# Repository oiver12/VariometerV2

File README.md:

# VariometerV2

A paragliding variometer built from custom KiCad PCBs, ESP32 firmware, sensor fusion, and an e-ink flight interface.

Flight-tested on my paragliding harness. [Watch the flight video](docs/media/flight.mp4).

I started this project in 2021 as my [**Maturarbeit**](https://github.com/oiver12/Variometer-Maturarbeit) (Swiss high-school thesis), then continued developing it independently through 2024. I designed the custom PCBs and developed the firmware, sensor fusion pipeline, and e-ink rendering system, screens, and widgets. The enclosure/CAD work combines contributions from my brother and me.

## Features

- Three custom PCB revisions designed in KiCad.
- ESP32 firmware in C on ESP-IDF and FreeRTOS.
- BMI088 IMU, DPS310 barometer, and QMC5883L magnetometer; quaternion orientation estimation and a Kalman filter combining barometric altitude with acceleration.
- GPS/NMEA input, IGC flight logging, airspace parsing, sound output, an experimental BLE module, and watchdog support.
- E-ink UI with a custom rendering system, screens, and widgets.
- Sensor mocks, a FreeRTOS host simulation, a Linux screen simulator, and recorded-sensor replay for analysis.

## Hardware

### Latest revision: 2.1

| Front / top | Back / mirrored bottom |
| --- | --- |
|  |  |

[Schematic overview](docs/images/schematic-2.1/VariometerV2.2.1.svg) · [Power](docs/images/schematic-2.1/VariometerV2.2.1-Power.svg) · [Sensors](docs/images/schematic-2.1/VariometerV2.2.1-Devices.svg) · [Display](docs/images/schematic-2.1/VariometerV2.2.1-Screen.svg) · [Peripherals](docs/images/schematic-2.1/VariometerV2.2.1-Peripherals.svg)

### Revision history

| Revision | Design files | PCB views | Schematic |
| --- | --- | --- | --- |
| 1.0 | [Hardware/Version 1.0](Hardware/Version%201.0/) | [Top](docs/images/pcb-1.0-top.svg) · [bottom](docs/images/pcb-1.0-bottom.svg) · [3D](docs/images/pcb-1.0-3d.png) | [SVG](docs/images/schematic-1.0/VariometerV2.svg) |
| 2.0 | [Hardware/Version 2.0](Hardware/Version%202.0/) | [Top](docs/images/pcb-2.0-top.svg) · [bottom](docs/images/pcb-2.0-bottom.svg) · [3D](docs/images/pcb-2.0-3d.png) | [SVG](docs/images/schematic-2.0/VariometerV2.2.svg) |
| 2.1 | [Hardware/Version 2.1](Hardware/Version%202.1/) | [Top](docs/images/pcb-2.1-top.svg) · [bottom](docs/images/pcb-2.1-bottom.svg) · [3D](docs/images/pcb-2.1-3d.png) | [SVG overview](docs/images/schematic-2.1/VariometerV2.2.1.svg) |

`Case/` contains the enclosure designs and printing exports.

## Firmware architecture

```mermaid
flowchart LR
    IMU["BMI088 IMU"] --> Drivers["Sensor drivers"]
    Baro["DPS310 barometer"] --> Drivers
    Mag["QMC5883L magnetometer"] --> Drivers
    Drivers --> Orientation["Quaternion orientation"]
    Orientation --> Acc["Vertical acceleration"]
    Drivers --> Kalman["Kalman altitude and climb rate"]
    Acc --> Kalman
    GPS["GPS / NMEA"] --> State["Flight state / device context"]
    Kalman --> State
    Airspace["Airspace parser"] --> State
    State --> UI["E-ink UI / screens / widgets"]
    State --> IGC["IGC logger"]
    State --> BLE["BLE module (experimental)"]
    State --> Sound["Sound"]
```

The sensor fusion pipeline runs across FreeRTOS tasks: the barometer task notifies the Kalman filter, while the acceleration task updates orientation and queues vertical acceleration. The filter combines these inputs into shared flight state, using queues, task notifications, and mutexes to coordinate the tasks.

Rendering and e-ink refresh run in separate tasks. GPS parsing, IGC logging, button input, battery management, sound, storage checks, and airspace parsing have their own task entry points.

### Project structure

| Directory | Purpose |
| --- | --- |
| `Hardware/`, `Case/` | PCB revisions and enclosure designs |
| `Software/variometer-software/` | ESP32 firmware |
| `Simulation/Main/` | FreeRTOS host runner and sensor mocks |
| `Screen_Simulator_Linux/`, `Screen_Simulator/` | Desktop UI simulators |
| `VariometerAnalysis/` | Sensor-log analysis and offline replay |

## Simulation & replay

Sensor mocks replace hardware reads with recorded IMU, magnetometer, and pressure samples. A FreeRTOS simulation replays these recordings on a PC, allowing the firmware to run against recorded data.

The offline analysis tool runs the firmware’s quaternion and Kalman functions over the recorded sensor data:

Barometric altitude and climb rate compared with the Kalman estimate. The recording has no timestamps, so replay uses an assumed sample interval; this plot is not a latency benchmark.

The Linux screen simulator exercises the custom UI independently of the device:

| Flight layout | Navigation layout | Settings |
| --- | --- | --- |
|  |  |  |

[Replay and simulator instructions](docs/development.md#simulation--replay).

## Build & flash

**ESP32-S3 · ESP-IDF v5.1.4**

See the [developer guide](docs/development.md) for cloning, firmware build and flash commands, desktop simulation, and regenerating the visuals.

## Flight footage

## Third-party code & license

The project builds on FreeRTOS, Waveshare’s e-ink driver and GUI, STMicroelectronics bitmap fonts, Neil Kolban’s BLE library, Freescale/NXPMotionSense sensor fusion, kalman-clib, and other credited libraries. Full credits and license details are in [THIRD_PARTY_NOTICES.txt](THIRD_PARTY_NOTICES.txt).

**My original software is licensed under [MIT](LICENSE).** Third-party code retains its own licenses, including the FIFO’s **GPL-3.0-or-later** obligations; the combined tree is not uniformly MIT-licensed. Enclosure/CAD contributions and third-party assets are outside this software license unless separately stated.

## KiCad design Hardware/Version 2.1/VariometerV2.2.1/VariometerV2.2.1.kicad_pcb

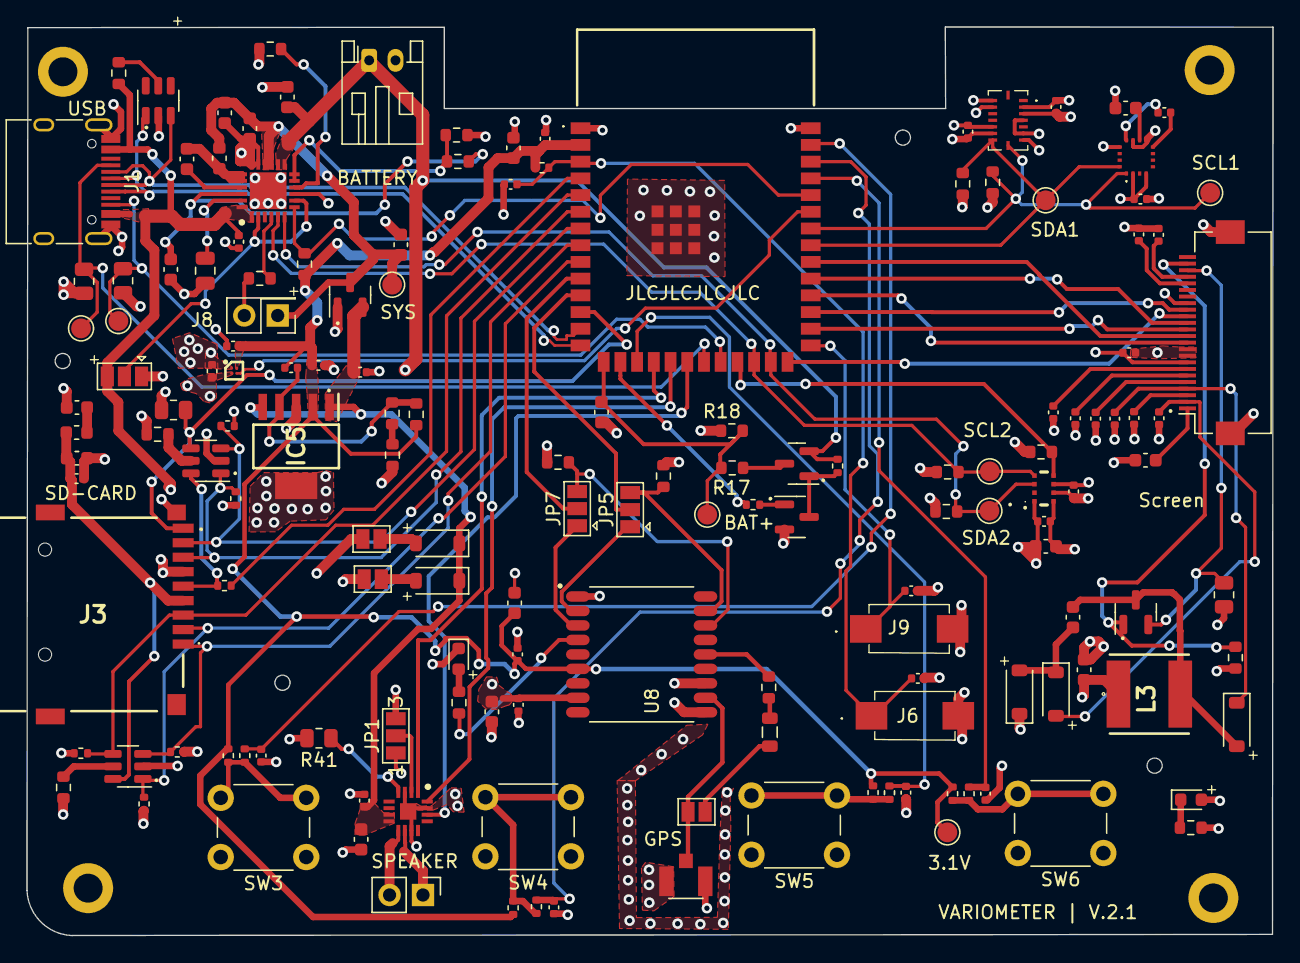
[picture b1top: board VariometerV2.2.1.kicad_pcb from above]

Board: 4 copper layers, 94.7 x 69.1 mm, 158 parts (0 on the bottom side), 100 nets.

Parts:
C1: 22uF; C_0603_1608Metric
C2, C6, C11, C15, C16, C19, C23, C24, C25, C26, C27, C28, C29, C31, C32, C47, C48, C49: 1uF; C_0402_1005Metric
C3, C4, C5, C8, C17, C20, C35, C36, C37, C38, C39, C43, C50: 100nF; C_0402_1005Metric
C7, C13, C14, C30, C42, C44, C45, C52: 10uF; C_0603_1608Metric
C9, C33, C34, C40, C46: 4.7uF; C_0603_1608Metric
C10: 6.8uF; C_0805_2012Metric
C12: 47nF; C_0603_1608Metric
C18: 10nF; C_0402_1005Metric
C21, C22: 2.2uF; C_0603_1608Metric
C41: 220nF; C_0402_1005Metric
C51: 1uF; C_0603_1608Metric
D1, D3, D4, D5, D6: B5819W SL; D_SOD-123
D2: RED; LED_0603_1608Metric
D7: BLUE; LED_0603_1608Metric
FB1: 600 @ 100 MHz; L_0603_1608Metric
H1, H2, H3, H4: MountingHole_Pad; MountingHole_2.2mm_M2_DIN965_Pad
IC1: ESP32-S3-WROOM; ESP32S3WROOM1
IC3: BQ24196RGER; QFN50P400X400X100-25N-D
IC4: TPS22916CNYFPR; BGA4C40P2X2_78X78X50
IC5: TPS73701DCQR; SOT127P706X180-6N
J1: USB_C_Receptacle_USB2.0; USB_C_Receptacle_HRO_TYPE-C-31-M-12
J2: Conn_01x02; PinHeader_1x02_P2.54mm_Vertical
J3: TFP09212B
J5: U.FL-R-SMT(01); HRS_U.FL-R-SMT(01)
J6, J9: SW; PTS636SM25FSMTRLFS
J7: Conn_01x02; JST_PH_S2B-PH-K_1x02_P2.00mm_Horizontal
J8: LED_CHRG; PinHeader_2x01_P2.54mm_Vertical
J10: Conn_01x24_MountingPin; Hirose_FH12-24S-0.5SH_1x24-1MP_P0.50mm_Horizontal
JP1: SolderJumper_3_Open; SolderJumper-3_P1.3mm_Open_Pad1.0x1.5mm_NumberLabels
JP2, JP4: JMP; SolderJumper-2_P1.3mm_Open_Pad1.0x1.5mm
JP5, JP7: SolderJumper-3_P1.3mm_Open_Pad1.0x1.5mm
JP6: SJ; SolderJumper-2_P1.3mm_Open_Pad1.0x1.5mm
JP8: SJMP; SolderJumper-3_P1.3mm_Open_Pad1.0x1.5mm
L1: 1uH P; L_0603_1608Metric
L2: 47nH; L_0805_2012Metric
L3: SRN6045TA-680M; SRN6045TA
Q1, Q2: AO3401A; SOT-23
Q3, Q4: AO3400A; SOT-23
R1, R5, R20, R27, R28, R29, R30, R31, R44, R46, R48: 10k; R_0402_1005Metric
R2, R3: 5.1k; R_0805_2012Metric
R4, R7, R8, R15, R17, R25, R26, R35, R37, R38, R39, R40, R42, R43: 10k; R_0603_1608Metric
R6, R45, R47, R49: 1k; R_0402_1005Metric
R9, R13: 1k; R_0603_1608Metric
R10: 10R; R_0603_1608Metric
R16: 270R; R_0603_1608Metric
R18: 15k; R_0603_1608Metric
R19: 1M; R_0402_1005Metric
R21: 47k; R_0603_1608Metric
R22: 20k; R_0603_1608Metric
R23: 9.1k; R_0603_1608Metric
R24: 1.5k; R_0603_1608Metric
R32: 10k S; R_0805_2012Metric
R33: 22; R_0402_1005Metric
R34: 0.47R; R_0805_2012Metric
R36: 100k; R_0603_1608Metric
R41: 10k B; R_0805_2012Metric
SW3, SW4, SW5, SW6: BTN1; SW_PUSH_6mm_H4.3mm
TP1: TP_BATTERY; TestPoint_Pad_D1.5mm
TP2: 3.1V TP; TestPoint_Pad_D1.5mm
TP3: TP_SDA1; TestPoint_Pad_D1.5mm
TP4: TP_SCL1; TestPoint_Pad_D1.5mm
TP5: TP_SDA2; TestPoint_Pad_D1.5mm
TP6: TP_SCL2; TestPoint_Pad_D1.5mm
TP10: TP_SYS_LOAD; TestPoint_Pad_D1.5mm
TP11: CC1; TestPoint_Pad_D1.5mm
TP12: CC2; TestPoint_Pad_D1.5mm
U1, U2, U3: SRV05-4; SOT-23-6
U4: DPS310; DPS310XTSA1
U5: BMI088
U6: QMC5883L
U7: MAX98357A; QFN50P300X300X80-17N
U8: L76-L; XCVR_L76-L

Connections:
3.1V_SDCARD: C20.1, C21.1, FB1.1, J3.4 (VDD), U2.6 (IO4)
+3.1V_SW: C7.1, C8.1, C17.1, C24.2, C33.1, C35.1, C36.1, C37.1, C38.1, C39.1, C52.1, D2.2 (A), IC4.A1 (VOUT), J10.9, J10.10, JP1.1 (A), L3.1, R7.1, R8.1, R25.1, R26.1, R27.1, R28.1, R29.1, R30.1, R31.1, R32.1, R37.1, R38.1, R39.1, R40.1, R41.1, U4.6 (VDDIO), U4.8 (VDD), U5.3 (VDD), U5.7 (PS), U5.11 (VDDIO), U5.14 (CSB1), U6.2 (VDD), U6.4 (S1), U6.13 (VDDIO), U7.4 (SD_MODE), U8.8 (VCC)
+3.1V_UNSW: C1.1, C3.1, C9.1, C15.1, C18.1, C19.1, C50.1, IC1.2 (3V3), IC4.A2 (VIN), IC5.2 (Vout), R1.1, R5.1, R15.1, R21.1, R44.1, R46.1, R48.1, TP2.1, U8.6 (V_BCKP)
+3.3V: C22.1, FB1.2
+5V: C11.1, IC3.1 (VBUS1), IC3.24 (VBUS2), J1.A4 (VBUS), J1.A9 (VBUS), J1.B4 (VBUS), J1.B9 (VBUS), JP2.2 (B), JP8.3 (B), R4.1
+BATT: C13.1, IC3.13 (BAT1), IC3.14 (BAT2), J7.1, JP4.2 (B), Q2.2 (S), R19.2
/Devices/GPS_RX: JP7.1 (A), U8.3 (RXD)
/Devices/GPS_SCL: JP5.3 (B), R8.2, U8.17 (I2C_SCL)
/Devices/GPS_SDA: JP7.3 (B), R7.2, U8.16 (I2C_SDA)
/Devices/GPS_TX: JP5.1 (A), U8.2 (TXD)
/Devices/GPS_VCCREF: R10.2, U8.14 (VCC_RF)
/Power/REGN: C46.1, IC3.22 (REGN), R42.1
/Power/STAT: IC3.4 (STAT), R13.2
/Power/SYS: C14.1, C44.1, C45.1, IC3.15 (SYS1), IC3.16 (SYS2), J8.1, L1.2, Q1.3 (D), TP10.1
/Power/TS: IC3.11 (TS1), IC3.12 (TS2), R42.2, R43.1
/Screen/GDR: J10.23, Q4.1 (G), R35.2
/Screen/PREVGH: C27.2, D3.1 (K), J10.4
/Screen/PREVGL: C29.2, D4.2 (A), J10.2
/Screen/RESE: J10.22, Q4.2 (S), R34.2
AUDIO_OUTN: J2.1, U7.10 (OUTN)
AUDIO_OUTP: J2.2, U7.9 (OUTP)
BAT_ADC: C51.1, IC1.15 (IO3), R17.1, R18.2, TP1.1
BAT_MS: IC1.16 (IO46), R20.1
BUTTON_1: C6.1, IC1.39 (IO1), R6.2
BUTTON_2: C47.1, IC1.38 (IO2), R45.2
BUTTON_3: C48.1, IC1.17 (IO9), R47.2
BUTTON_4: C49.1, IC1.37 (TXD0), R49.2
CHARG_INT: IC1.36 (RXD0), IC3.7 (INT), R15.2
EN: C2.1, C4.1, IC1.3 (EN), J6.1 (COM), R1.2
GND: C1.2, C2.2, C3.2, C4.2, C5.2, C6.2, C7.2, C8.2, C9.2, C10.2, C11.2, C13.2, C14.2, C15.2, C16.2, C17.2, C19.2, C20.2, C21.2, C22.2, C23.1, C24.1, C25.1, C26.1, C27.1, C28.1, C29.1, C30.1, C31.1, C32.1, C33.2, C35.2, C36.2, C37.2, C38.2, C39.2, C40.2, C42.2, C43.2, C44.2, C45.2, C46.2, C47.2, C48.2, C49.2, C50.2, C51.2, C52.2, D5.1 (K), D7.1 (K), H1.1, H2.1, H3.1, H4.1, IC1.1 (GND_1), IC1.40 (GND_2), IC1.41 (GND_3), IC1.42 (GND_4), IC1.43 (GND_5), IC1.44 (GND_6), IC1.45 (GND_7), IC1.46 (GND_8), IC1.47 (GND_9), IC1.48 (GND_10), IC1.49 (GND_11), IC3.9 (~CE), IC3.17 (PGND), IC3.18 (PGND), IC3.25 (EP), IC4.B1 (GND), IC5.3 (GND_1), IC5.6 (GND_2), J1.A1 (GND), J1.A12 (GND), J1.B1 (GND), J1.B12 (GND), J1.S1 (SHIELD), J3.6 (VSS), J3.G1 (GND), J5.1 (GND), J5.2 (GND), J6.2 (NO), J7.2, J9.2 (NO), J10.8, J10.17, J10.MP (MountPin), JP1.3 (B), JP8.1 (A), Q1.1 (G), Q3.2 (S), R2.2, R3.2, R16.2, R18.1, R23.2, R24.2, R34.1, R35.1, R36.2, R41.2, R43.2, SW3.1, SW4.1, SW5.1, SW6.1, U1.2 (VN), U2.2 (VN), U3.2 (VN), U4.1 (GND), U4.7 (GND), U5.2 (NC), U5.4 (GNDA), U5.6 (GNDIO), U5.10 (SDO2), U5.15 (SDO1), U6.9 (GND), U6.11 (GND), U7.3 (GND), U7.11 (GND), U7.15 (GND), U7.17 (EP), U8.1 (GND), U8.10 (GND), U8.12 (GND)
I2C1_SCL: IC1.34 (IO41), R38.2, TP4.1, U5.8 (SCK), U6.1 (SCL)
I2C1_SDA: IC1.33 (IO40), R37.2, TP3.1, U5.9 (SDI), U6.16 (SDA)
I2C2_SCL: IC1.24 (IO47), IC3.5 (SCL), R40.2, TP6.1, U4.4 (SCK)
I2C2_SDA: IC1.25 (IO48), IC3.6 (SDA), R39.2, TP5.1, U4.3 (SDI)
I2S_BCLK: IC1.19 (IO11), U7.16 (BCLK)
I2S_DIN: IC1.18 (IO10), U7.1 (DIN)
I2S_LRCLK: IC1.20 (IO12), U7.14 (LRCLK)
IO0: C5.1, IC1.27 (IO0), J9.1 (COM)
LCD_BUSY: IC1.29 (IO36), J10.16
LCD_CLK: IC1.32 (IO39), J10.12
LCD_CS: IC1.28 (IO35), J10.13
LCD_DC: IC1.31 (IO38), J10.14
LCD_DIN: IC1.30 (IO37), J10.11
LCD_RST: IC1.26 (IO45), J10.15
unnamed: D1.2 (A), JP2.1 (A)
unnamed: D2.1 (K), R24.1
unnamed: C34.1, D3.2 (A), L3.2, Q4.3 (D)
unnamed: C34.2, D4.1 (K), D5.2 (A)
unnamed: D6.2 (A), JP4.1 (A)
unnamed: D7.2 (A), R9.2
unnamed: C12.2, IC3.21 (BTST)
unnamed: IC3.10 (ILIM), R16.1
unnamed: IC3.2 (PSEL), IC3.8 (OTG), JP8.2 (C)
unnamed: C10.1, IC3.23 (PMID)
unnamed: C12.1, IC3.19 (SW1), IC3.20 (SW2), L1.1
unnamed: C18.2, IC5.4 (FB), R21.2, R22.1
unnamed: J3.5 (CLK), R33.2, U3.6 (IO4)
unnamed: J5.3 (SIG), JP6.1 (A), U8.11 (RF_IN)
unnamed: J8.2, R13.1
unnamed: C30.2, J10.1
unnamed: C28.2, J10.3
unnamed: C26.2, J10.5
unnamed: C25.2, J10.6
unnamed: C23.2, J10.7
unnamed: C32.2, J10.20
unnamed: C31.2, J10.21
unnamed: JP1.2 (C), U7.2 (GAIN)
unnamed: JP6.2 (B), L2.1
unnamed: L2.2, R10.1
unnamed: Q2.3 (D), R17.2
unnamed: Q2.1 (G), Q3.3 (D), R19.1
unnamed: Q3.1 (G), R20.2
unnamed: R5.2, R6.1, SW3.2
unnamed: R22.2, R23.1
unnamed: R44.2, R45.1, SW4.2
unnamed: R46.2, R47.1, SW5.2
unnamed: R48.2, R49.1, SW6.2
unnamed: R4.2, U1.5 (VP)
unnamed: R25.2, U2.5 (VP)
unnamed: R26.2, U3.5 (VP)
unnamed: C40.1, U6.10 (C1)
unnamed: C41.2, U6.12 (SETC)
unnamed: C41.1, U6.8 (SETP)
unnamed: R9.1, U8.4 (1PPS)
POSW_EN: IC1.35 (IO42), IC4.B2 (ON)
PrSen_INT: IC1.23 (IO21), R36.1, U4.5 (SDO)
SD_CD: IC1.12 (IO8), J3.CD1 (DET), R32.2, U3.4 (IO3)
SD_CLK: IC1.4 (IO4), R33.1
SD_CMD: IC1.5 (IO5), J3.3 (CMD), R29.2, U2.4 (IO3)
SD_DAT0: IC1.6 (IO6), J3.7 (DAT0), R30.2, U3.1 (IO1)
SD_DAT1: IC1.7 (IO7), J3.8 (DAT1), R31.2, U3.3 (IO2)
SD_DAT2: IC1.8 (IO15), J3.1 (DAT2), R27.2, U2.3 (IO2)
SD_DAT3: IC1.9 (IO16), J3.2 (DAT3/CD), R28.2, U2.1 (IO1)
USART2_RX: IC1.11 (IO18), JP5.2 (C)
USART2_TX: IC1.10 (IO17), JP7.2 (C)
USB_CC1: IC1.21 (IO13), J1.A5 (CC1), R3.1, TP11.1
USB_CC2: IC1.22 (IO14), J1.B5 (CC2), R2.1, TP12.1
USB_D+: IC1.14 (IO20), J1.A6 (D+), J1.B6 (D+), U1.1 (IO1)
USB_D-: IC1.13 (IO19), J1.A7 (D-), J1.B7 (D-), U1.3 (IO2)
VCC: C16.1, C42.1, C43.1, D1.1 (K), D6.1 (K), IC5.1 (Vin), IC5.5 (EN), Q1.2 (S), U7.7 (VDD), U7.8 (VDD)

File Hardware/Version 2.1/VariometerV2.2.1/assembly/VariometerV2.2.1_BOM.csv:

Comment,Designator,Footprint,LCSC Part #
"22uF Unpolarized capacitor, small symbol",C1,C_0603_1608Metric,C59461
"1uF Unpolarized capacitor, small symbol","C2,C6,C11,C15,C16,C19,C23,C24,C25,C26,C27,C28,C29,C31,C32,C47,C48,C49",C_0402_1005Metric,C52923
"100nF Unpolarized capacitor, small symbol","C3,C4,C5,C8,C17,C20,C35,C36,C37,C38,C39,C43,C50",C_0402_1005Metric,C307331
"10uF Unpolarized capacitor, small symbol","C7,C13,C14,C30,C42,C44,C45,C52",C_0603_1608Metric,C19702
"4.7uF Unpolarized capacitor, small symbol","C9,C33,C34,C40,C46",C_0603_1608Metric,C19666
"6.8uF Unpolarized capacitor, small symbol",C10,C_0805_2012Metric,0
"47nF Unpolarized capacitor, small symbol",C12,C_0603_1608Metric,C1622
"10nF Unpolarized capacitor, small symbol",C18,C_0402_1005Metric,C15195
"2.2uF Unpolarized capacitor, small symbol","C21,C22",C_0603_1608Metric,C23630
"220nF Unpolarized capacitor, small symbol",C41,C_0402_1005Metric,C16772
"1uF Unpolarized capacitor, small symbol",C51,C_0603_1608Metric,C15849
"B5819W SL Schottky diode, small symbol","D1,D3,D4,D5,D6",D_SOD-123,C8598
"RED Light emitting diode, small symbol",D2,LED_0603_1608Metric,C2286
BLUE Light emitting diode,D7,LED_0603_1608Metric,C72041
"600 @ 100 MHz Ferrite bead, small symbol",FB1,L_0603_1608Metric,C1002
MountingHole_Pad Mounting Hole with connection,"H1,H2,H3,H4",MountingHole_2.2mm_M2_DIN965_Pad,0
ESP32-S3-WROOM ,IC1,ESP32S3WROOM1,C2913198
BQ24196RGER I2C Controlled 2.5A Single Cell USB/Adaptor Charger w/ Narrow VDC Power Path,IC3,QFN50P400X400X100-25N-D,C117006
TPS22916CNYFPR ,IC4,BGA4C40P2X2_78X78X50,C2655476
TPS73701DCQR ,IC5,SOT127P706X180-6N,C56848
USB_C_Receptacle_USB2.0 USB 2.0-only Type-C Receptacle connector,J1,USB_C_Receptacle_HRO_TYPE-C-31-M-12,C165948
"Conn_01x02 Generic connector, single row, 01x02, script generated (kicad-library-utils/schlib/autogen/connector/)",J2,PinHeader_1x02_P2.54mm_Vertical,0
~ ,J3,TFP09212B,0
U.FL-R-SMT(01) ,J5,HRS_U.FL-R-SMT(01),0
SW ,"J6,J9",PTS636SM25FSMTRLFS,0
"Conn_01x02 Generic connector, single row, 01x02, script generated (kicad-library-utils/schlib/autogen/connector/)",J7,JST_PH_S2B-PH-K_1x02_P2.00mm_Horizontal,0
"LED_CHRG Generic connector, double row, 02x01, this symbol is compatible with counter-clockwise, top-bottom and odd-even numbering schemes., script generated (kicad-library-utils/schlib/autogen/connector/)",J8,PinHeader_2x01_P2.54mm_Vertical,0
"Conn_01x24_MountingPin Generic connectable mounting pin connector, single row, 01x24, script generated (kicad-library-utils/schlib/autogen/connector/)",J10,Hirose_FH12-24S-0.5SH_1x24-1MP_P0.50mm_Horizontal,C519265
"SolderJumper_3_Open Solder Jumper, 3-pole, open",JP1,SolderJumper-3_P1.3mm_Open_Pad1.0x1.5mm_NumberLabels,0
"JMP Solder Jumper, 2-pole, open","JP2,JP4",SolderJumper-2_P1.3mm_Open_Pad1.0x1.5mm,0
"~ Solder Jumper, 3-pole, open","JP5,JP7",SolderJumper-3_P1.3mm_Open_Pad1.0x1.5mm,0
"SJ Solder Jumper, 2-pole, open",JP6,SolderJumper-2_P1.3mm_Open_Pad1.0x1.5mm,0
"SJMP Solder Jumper, 3-pole, open",JP8,SolderJumper-3_P1.3mm_Open_Pad1.0x1.5mm,0
"1uH P Inductor, small symbol",L1,L_0603_1608Metric,0
"47nH Inductor, small symbol",L2,L_0805_2012Metric,C162657
SRN6045TA-680M SRN6045TA Series - Semi-shielded Power Inductors,L3,SRN6045TA,0
"AO3401A -4.0A Id, -30V Vds, P-Channel MOSFET, SOT-23","Q1,Q2",SOT-23,C15127
"AO3400A 30V Vds, 5.7A Id, N-Channel MOSFET, SOT-23","Q3,Q4",SOT-23,C20917
"10k Resistor, small symbol","R1,R5,R20,R27,R28,R29,R30,R31,R44,R46,R48",R_0402_1005Metric,C25744
"5.1k Resistor, small symbol","R2,R3",R_0805_2012Metric,C27834
"10k Resistor, small symbol","R4,R7,R8,R15,R17,R25,R26,R35,R37,R38,R39,R40,R42,R43",R_0603_1608Metric,C25804
"1k Resistor, small symbol","R6,R45,R47,R49",R_0402_1005Metric,C11702
"1k Resistor, small symbol","R9,R13",R_0603_1608Metric,C21190
"10R Resistor, small symbol",R10,R_0603_1608Metric,C22859
"270R Resistor, small symbol",R16,R_0603_1608Metric,C22966
"15k Resistor, small symbol",R18,R_0603_1608Metric,C22809
"1M Resistor, small symbol",R19,R_0402_1005Metric,C26083
"47k Resistor, small symbol",R21,R_0603_1608Metric,C25819
"20k Resistor, small symbol",R22,R_0603_1608Metric,C4184
"9.1k Resistor, small symbol",R23,R_0603_1608Metric,C23260
"1.5k Resistor, small symbol",R24,R_0603_1608Metric,C22843
"10k S Resistor, small symbol",R32,R_0805_2012Metric,C17414
"22 Resistor, small symbol",R33,R_0402_1005Metric,C25092
"0.47R Resistor, small symbol",R34,R_0805_2012Metric,0
"100k Resistor, small symbol",R36,R_0603_1608Metric,C25803
"10k B Resistor, small symbol",R41,R_0805_2012Metric,C17414
BTN1 ,"SW3,SW4,SW5,SW6",SW_PUSH_6mm_H4.3mm,0
TP_BATTERY test point,TP1,TestPoint_Pad_D1.5mm,0
3.1V TP test point,TP2,TestPoint_Pad_D1.5mm,0
TP_SDA1 test point,TP3,TestPoint_Pad_D1.5mm,0
TP_SCL1 test point,TP4,TestPoint_Pad_D1.5mm,0
TP_SDA2 test point,TP5,TestPoint_Pad_D1.5mm,0
TP_SCL2 test point,TP6,TestPoint_Pad_D1.5mm,0
TP_SYS_LOAD test point,TP10,TestPoint_Pad_D1.5mm,0
CC1 test point,TP11,TestPoint_Pad_D1.5mm,0
CC2 test point,TP12,TestPoint_Pad_D1.5mm,0
"SRV05-4 ESD Protection Diodes with Low Clamping Voltage, SOT-23-6","U1,U2,U3",SOT-23-6,C85364
DPS310 ,U4,DPS310XTSA1,C130156
BMI088 ,U5,BMI088,C194919
QMC5883L ,U6,QMC5883L,C976032
MAX98357A ,U7,QFN50P300X300X80-17N,C910544
L76-L ,U8,XCVR_L76-L,0

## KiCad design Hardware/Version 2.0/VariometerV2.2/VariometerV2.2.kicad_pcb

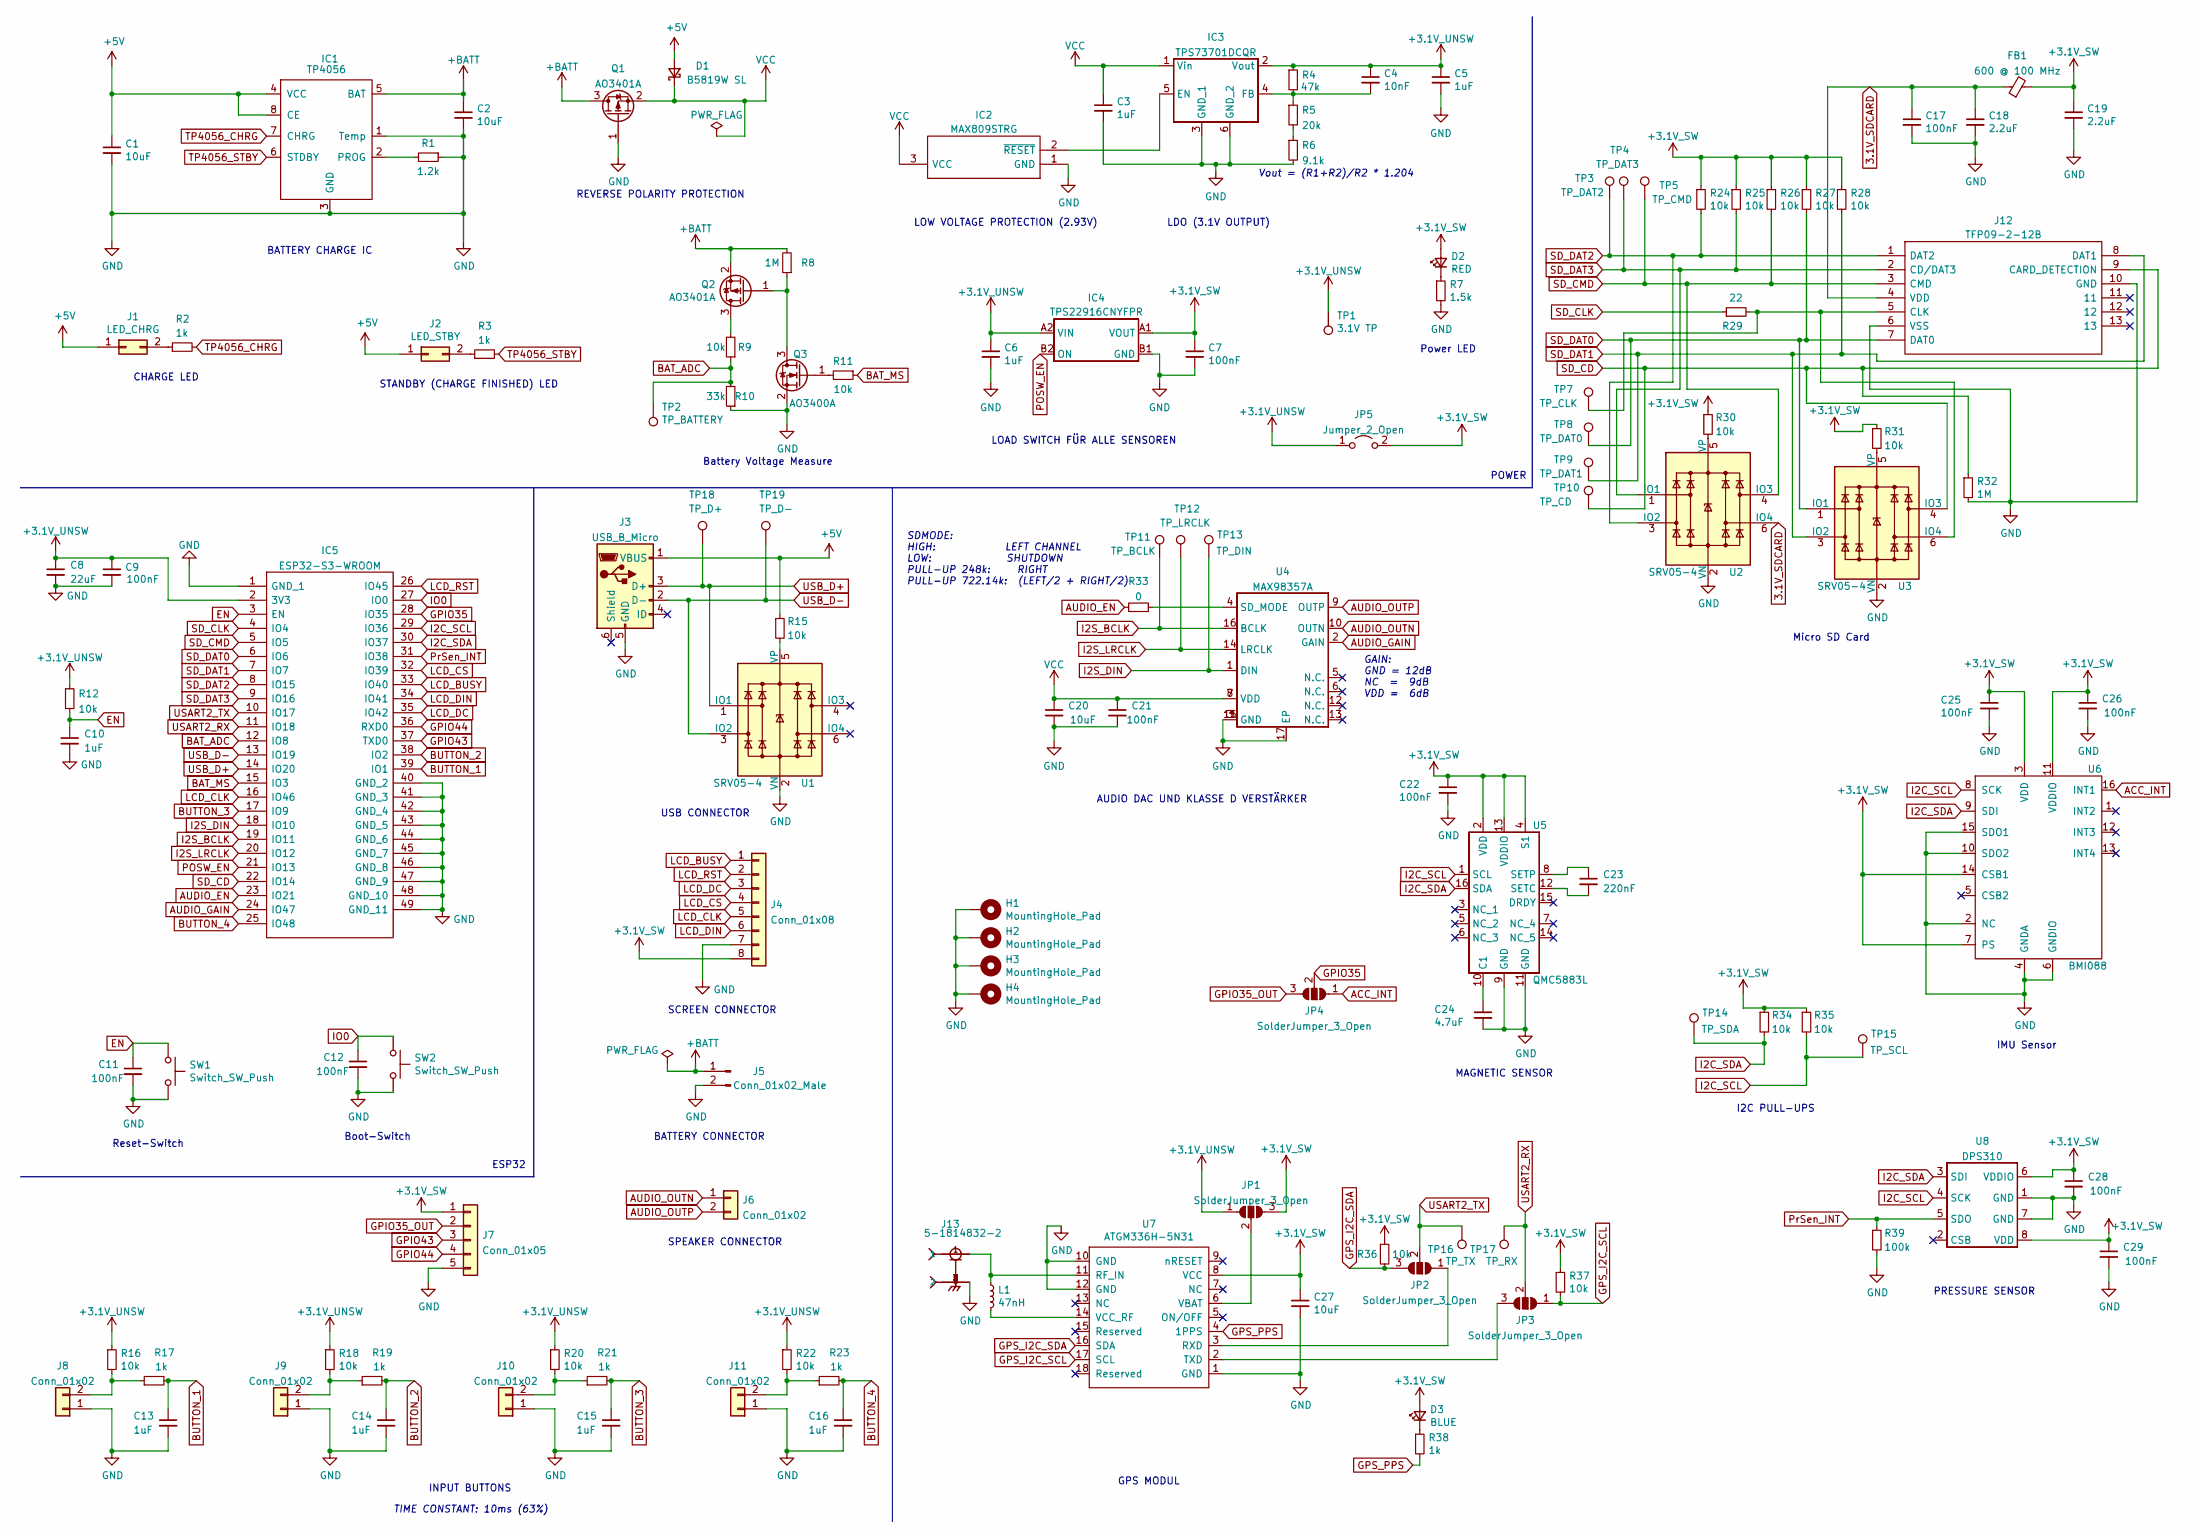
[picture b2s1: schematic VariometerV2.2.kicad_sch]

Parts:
C1, C2, C20, C27: 10uF; C_0603_1608Metric; JLCPCB Part # C96446
C3, C5, C6, C10: 1uF; C_0402_1005Metric; JLCPCB Part # C52923
C4: 10nF; C_0402_1005Metric; JLCPCB Part # C15195
C7, C9, C12, C17, C21, C22, C25, C26, C28, C29: 100nF; C_0402_1005Metric; JLCPCB Part # C307331
C8: 22uF; C_0603_1608Metric; JLCPCB Part # C59461
C11: 100nF; C_0603_1608Metric; JLCPCB Part # C14663
C13, C14, C15, C16: 1uF; C_0603_1608Metric; JLCPCB Part # C15849
C18, C19: 2.2uF; C_0603_1608Metric; JLCPCB Part # C23630
C23: 220nF; C_0402_1005Metric; JLCPCB Part # C16772
C24: 4.7uF; C_0603_1608Metric; JLCPCB Part # C19666
D1: B5819W SL; D_SOD-123; JLCPCB Part # C8598
D2: RED; LED_0603_1608Metric; JLCPCB Part # C2286
D3: BLUE; LED_0603_1608Metric; JLCPCB Part # C72041
FB1: 600 @ 100 MHz; L_0603_1608Metric; JLCPCB Part # C1002
H1, H2, H3, H4: MountingHole_Pad; MountingHole_2.2mm_M2_DIN965_Pad
IC1: TP4056; SOIC127P600X175-9N; JLCPCB Part # C16581
IC2: MAX809STRG; SOT96P237X111-3N; Mouser Part Number 863-MAX809STRG
IC3: TPS73701DCQR; SOT127P706X180-6N; JLCPCB Part # C56848
IC4: TPS22916CNYFPR; BGA4C40P2X2_78X78X50; JLCPCB Part # C2655476
IC5: ESP32-S3-WROOM; ESP32S3WROOM1; Manufacturer_Part_Number ESP32-S3-WROOM-1; JLCPCB Part # C2913198
J1: LED_CHRG; PinHeader_2x01_P2.00mm_Vertical
J2: LED_STBY; PinHeader_2x01_P2.00mm_Vertical
J3: USB_B_Micro; USB313530A
J4: Conn_01x08; PinHeader_1x08_P2.54mm_Vertical
J5: Conn_01x02_Male; PinHeader_1x02_P2.54mm_Vertical
J6, J8, J9, J10, J11: Conn_01x02; PinHeader_1x02_P2.54mm_Vertical
J7: Conn_01x05; PinHeader_1x05_P2.54mm_Vertical
J12: TFP09-2-12B; TFP09212B; Manufacturer_Part_Number TFP09-2-12B
J13: 5-1814832-2; 518148322
JP1, JP2, JP3, JP4: SolderJumper_3_Open; SolderJumper-3_P1.3mm_Open_RoundedPad1.0x1.5mm_NumberLabels
JP5: Jumper_2_Open; TestPoint_2Pads_Pitch2.54mm_Drill0.8mm
L1: 47nH; L_0603_1608Metric; JLCPCB Part # C346317
Q1, Q2: AO3401A; SOT-23; JLCPCB Part # C15127
Q3: AO3400A; SOT-23; JLCPCB Part # C20917
R1: 1.2k; R_0805_2012Metric; JLCPCB Part # C17379
R2, R3, R17, R19, R21, R23, R38: 1k; R_0603_1608Metric; JLCPCB Part # C21190
R4: 47k; R_0603_1608Metric; JLCPCB Part # C25819
R5: 20k; R_0603_1608Metric; JLCPCB Part # C4184
R6: 9.1k; R_0603_1608Metric; JLCPCB Part # C23260
R7: 1.5k; R_0603_1608Metric; JLCPCB Part # C22843
R8, R32: 1M; R_0402_1005Metric; JLCPCB Part # C26083
R9, R11, R12, R15, R24, R25, R26, R27, R28, R30, R31, R34, R35: 10k; R_0402_1005Metric; JLCPCB Part # C25744
R10: 33k; R_0402_1005Metric; JLCPCB Part # C25779
R16, R18, R20, R22, R36, R37: 10k; R_0603_1608Metric; JLCPCB Part # C25804
R29: 22; R_0402_1005Metric; JLCPCB Part # C25092
R33: 0; R_0805_2012Metric; JLCPCB Part # C17477
R39: 100k; R_0402_1005Metric; JLCPCB Part # C25741
SW1, SW2: Switch_SW_Push; SW_PUSH_6mm
TP1: 3.1V TP; TestPoint_Pad_D1.5mm
TP2: TP_BATTERY; TestPoint_Pad_D1.5mm
TP3: TP_DAT2; TestPoint_Pad_D1.5mm
TP4: TP_DAT3; TestPoint_Pad_D1.5mm
TP5: TP_CMD; TestPoint_Pad_D1.5mm
TP7: TP_CLK; TestPoint_Pad_D1.5mm
TP8: TP_DAT0; TestPoint_Pad_D1.5mm
TP9: TP_DAT1; TestPoint_Pad_D1.5mm
TP10: TP_CD; TestPoint_Pad_D1.5mm
TP11: TP_BCLK; TestPoint_Pad_D1.5mm
TP12: TP_LRCLK; TestPoint_Pad_D1.5mm
TP13: TP_DIN; TestPoint_Pad_D1.5mm
TP14: TP_SDA; TestPoint_Pad_D1.5mm
TP15: TP_SCL; TestPoint_Pad_D1.5mm
TP16: TP_TX; TestPoint_Pad_D1.5mm
TP17: TP_RX; TestPoint_Pad_D1.5mm
TP18: TP_D+; TestPoint_Pad_D1.5mm
TP19: TP_D-; TestPoint_Pad_D1.5mm
U1, U2, U3: SRV05-4; SOT-23-6; JLCPCB Part # C85364
U4: MAX98357A; QFN50P300X300X80-17N; JLCPCB Part # C910544
U5: QMC5883L; JLCPCB Part # C976032
U6: BMI088; JLCPCB Part # C194919
U7: ATGM336H-5N31; ATGM336H5N31; JLCPCB Part # C90770
U8: DPS310; DPS310XTSA1; JLCPCB Part # C130156

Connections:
3.1V_SDCARD: C17.1, C18.1, FB1.1, J12.4 (VDD), U2.6 (IO4)
+3.1V_SW: C7.1, C19.1, C22.1, C25.1, C26.1, C27.1, C28.1, C29.1, D2.2 (A), D3.2 (A), FB1.2, IC4.A1 (VOUT), J4.8, J7.1, JP1.3 (B), JP5.2 (B), R24.1, R25.1, R26.1, R27.1, R28.1, R30.1, R31.1, R34.1, R35.1, R36.1, R37.1, U5.2 (VDD), U5.4 (S1), U5.13 (VDDIO), U6.3 (VDD), U6.7 (PS), U6.11 (VDDIO), U6.14 (CSB1), U7.8 (VCC), U8.6 (VDDIO), U8.8 (VDD)
+3.1V_UNSW: C4.1, C5.1, C6.1, C8.1, C9.1, IC3.2 (Vout), IC4.A2 (VIN), IC5.2 (3V3), JP1.1 (A), JP5.1 (A), R4.1, R12.1, R16.1, R18.1, R20.1, R22.1, TP1.1
+5V: C1.1, D1.2 (A), IC1.4 (VCC), IC1.8 (CE), J1.1, J2.1, J3.1 (VBUS), R15.1
+BATT: C2.1, IC1.5 (BAT), J5.1, Q1.3 (D), Q2.2 (S), R8.2
ACC_INT: JP4.1 (A), U6.16 (INT1)
AUDIO_EN: IC5.23 (IO21), R33.1
AUDIO_GAIN: IC5.24 (IO47), U4.2 (GAIN)
AUDIO_OUTN: J6.1, U4.10 (OUTN)
AUDIO_OUTP: J6.2, U4.9 (OUTP)
BAT_ADC: IC5.12 (IO8), R9.1, R10.2, TP2.1
BAT_MS: IC5.15 (IO3), R11.1
BUTTON_1: C13.1, IC5.39 (IO1), R17.2
BUTTON_2: C14.1, IC5.38 (IO2), R19.2
BUTTON_3: C15.1, IC5.17 (IO9), R21.2
BUTTON_4: C16.1, IC5.25 (IO48), R23.2
EN: C10.1, C11.1, IC5.3 (EN), R12.2, SW1.1
GND: C1.2, C2.2, C3.2, C5.2, C6.2, C7.2, C8.2, C9.2, C10.2, C11.2, C12.2, C13.2, C14.2, C15.2, C16.2, C17.2, C18.2, C19.2, C20.2, C21.2, C22.2, C24.2, C25.2, C26.2, C27.2, C28.2, C29.2, H1.1, H2.1, H3.1, H4.1, IC1.1 (Temp), IC1.3 (GND), IC2.1 (GND), IC3.3 (GND_1), IC3.6 (GND_2), IC4.B1 (GND), IC5.1 (GND_1), IC5.40 (GND_2), IC5.41 (GND_3), IC5.42 (GND_4), IC5.43 (GND_5), IC5.44 (GND_6), IC5.45 (GND_7), IC5.46 (GND_8), IC5.47 (GND_9), IC5.48 (GND_10), IC5.49 (GND_11), J3.5 (GND), J4.7, J5.2, J7.5, J8.1, J9.1, J10.1, J11.1, J12.6 (VSS), J12.10 (GND), J13.2, J13.3 (2), J13.4 (2), J13.5 (2), Q1.1 (G), Q3.2 (S), R1.1, R6.2, R7.2, R10.1, R32.2, R39.2, SW1.2, SW2.2, U1.2 (VN), U2.2 (VN), U3.2 (VN), U4.3 (GND), U4.11 (GND), U4.15 (GND), U4.17 (EP), U5.9 (GND), U5.11 (GND), U6.2 (NC), U6.4 (GNDA), U6.6 (GNDIO), U6.10 (SDO2), U6.15 (SDO1), U7.1 (GND), U7.10 (GND), U7.12 (GND), U8.1 (GND), U8.7 (GND)
GPIO35: IC5.28 (IO35), JP4.2 (C)
GPIO35_OUT: J7.2, JP4.3 (B)
GPIO43: IC5.37 (TXD0), J7.3
GPIO44: IC5.36 (RXD0), J7.4
GPS_I2C_SCL: JP3.1 (A), R37.2, U7.17 (SCL)
GPS_I2C_SDA: JP2.3 (B), R36.2, U7.16 (SDA)
GPS_PPS: R38.2, U7.4 (1PPS)
I2C_SCL: IC5.29 (IO36), R35.2, TP15.1, U5.1 (SCL), U6.8 (SCK), U8.4 (SCK)
I2C_SDA: IC5.30 (IO37), R34.2, TP14.1, U5.16 (SDA), U6.9 (SDI), U8.3 (SDI)
I2S_BCLK: IC5.19 (IO11), TP11.1, U4.16 (BCLK)
I2S_DIN: IC5.18 (IO10), TP13.1, U4.1 (DIN)
I2S_LRCLK: IC5.20 (IO12), TP12.1, U4.14 (LRCLK)
IO0: C12.1, IC5.27 (IO0), SW2.1
LCD_BUSY: IC5.33 (IO40), J4.1
LCD_CLK: IC5.16 (IO46), J4.5
LCD_CS: IC5.32 (IO39), J4.4
LCD_DC: IC5.35 (IO42), J4.3
LCD_DIN: IC5.34 (IO41), J4.6
LCD_RST: IC5.26 (IO45), J4.2
unnamed: C4.2, IC3.4 (FB), R4.2, R5.1
unnamed: C23.1, U5.8 (SETP)
unnamed: C23.2, U5.12 (SETC)
unnamed: C24.1, U5.10 (C1)
unnamed: D2.1 (K), R7.1
unnamed: D3.1 (K), R38.1
unnamed: IC1.2 (PROG), R1.2
unnamed: IC2.2 (~RESET), IC3.5 (EN)
unnamed: J1.2, R2.1
unnamed: J2.2, R3.1
unnamed: J8.2, R16.2, R17.1
unnamed: J9.2, R18.2, R19.1
unnamed: J10.2, R20.2, R21.1
unnamed: J11.2, R22.2, R23.1
unnamed: J12.5 (CLK), R29.2, TP7.1, U3.6 (IO4)
unnamed: J13.1, L1.1, U7.11 (RF_IN)
unnamed: JP1.2 (C), U7.6 (VBAT)
unnamed: JP2.1 (A), U7.3 (RXD)
unnamed: JP3.3 (B), U7.2 (TXD)
unnamed: L1.2, U7.14 (VCC_RF)
unnamed: Q2.1 (G), Q3.3 (D), R8.1
unnamed: Q2.3 (D), R9.2
unnamed: Q3.1 (G), R11.2
unnamed: R5.2, R6.1
unnamed: R15.2, U1.5 (VP)
unnamed: R30.2, U2.5 (VP)
unnamed: R31.2, U3.5 (VP)
unnamed: R33.2, U4.4 (SD_MODE)
POSW_EN: IC4.B2 (ON), IC5.21 (IO13)
PrSen_INT: IC5.31 (IO38), R39.1, U8.5 (SDO)
SD_CD: IC5.22 (IO14), J12.9 (CARD_DETECTION), R32.1, TP10.1, U3.4 (IO3)
SD_CLK: IC5.4 (IO4), R29.1
SD_CMD: IC5.5 (IO5), J12.3 (CMD), R26.2, TP5.1, U2.4 (IO3)
SD_DAT0: IC5.6 (IO6), J12.7 (DAT0), R27.2, TP8.1, U3.1 (IO1)
SD_DAT1: IC5.7 (IO7), J12.8 (DAT1), R28.2, TP9.1, U3.3 (IO2)
SD_DAT2: IC5.8 (IO15), J12.1 (DAT2), R24.2, TP3.1, U2.3 (IO2)
SD_DAT3: IC5.9 (IO16), J12.2 (CD/DAT3), R25.2, TP4.1, U2.1 (IO1)
TP4056_CHRG: IC1.7 (CHRG), R2.2
TP4056_STBY: IC1.6 (STDBY), R3.2
USART2_RX: IC5.11 (IO18), JP3.2 (C), TP17.1
USART2_TX: IC5.10 (IO17), JP2.2 (C), TP16.1
USB_D+: IC5.14 (IO20), J3.3 (D+), TP18.1, U1.1 (IO1)
USB_D-: IC5.13 (IO19), J3.2 (D-), TP19.1, U1.3 (IO2)
VCC: C3.1, C20.1, C21.1, D1.1 (K), IC2.3 (VCC), IC3.1 (Vin), Q1.2 (S), U4.7 (VDD), U4.8 (VDD)

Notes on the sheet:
Vout = (R1+R2)/R2 * 1.204
SDMODE: HIGH: LEFT CHANNEL LOW: SHUTDOWN PULL-UP 248k: RIGHT PULL-UP 722.14k: (LEFT/2 + RIGHT/2)
LDO (3.1V OUTPUT)
SCREEN CONNECTOR
Micro SD Card
REVERSE POLARITY PROTECTION
MAGNETIC SENSOR
GPS MODUL
BATTERY CHARGE IC
POWER
INPUT BUTTONS
LOW VOLTAGE PROTECTION (2.93V)
CHARGE LED
PRESSURE SENSOR
AUDIO DAC UND KLASSE D VERSTÄRKER
Boot-Switch
SPEAKER CONNECTOR
STANDBY (CHARGE FINISHED) LED
IMU Sensor
TIME CONSTANT: 10ms (63%)
Reset-Switch
USB CONNECTOR
BATTERY CONNECTOR
I2C PULL-UPS
GAIN: GND = 12dB NC = 9dB VDD = 6dB
Power LED
Battery Voltage Measure
ESP32
LOAD SWITCH FÜR ALLE SENSOREN

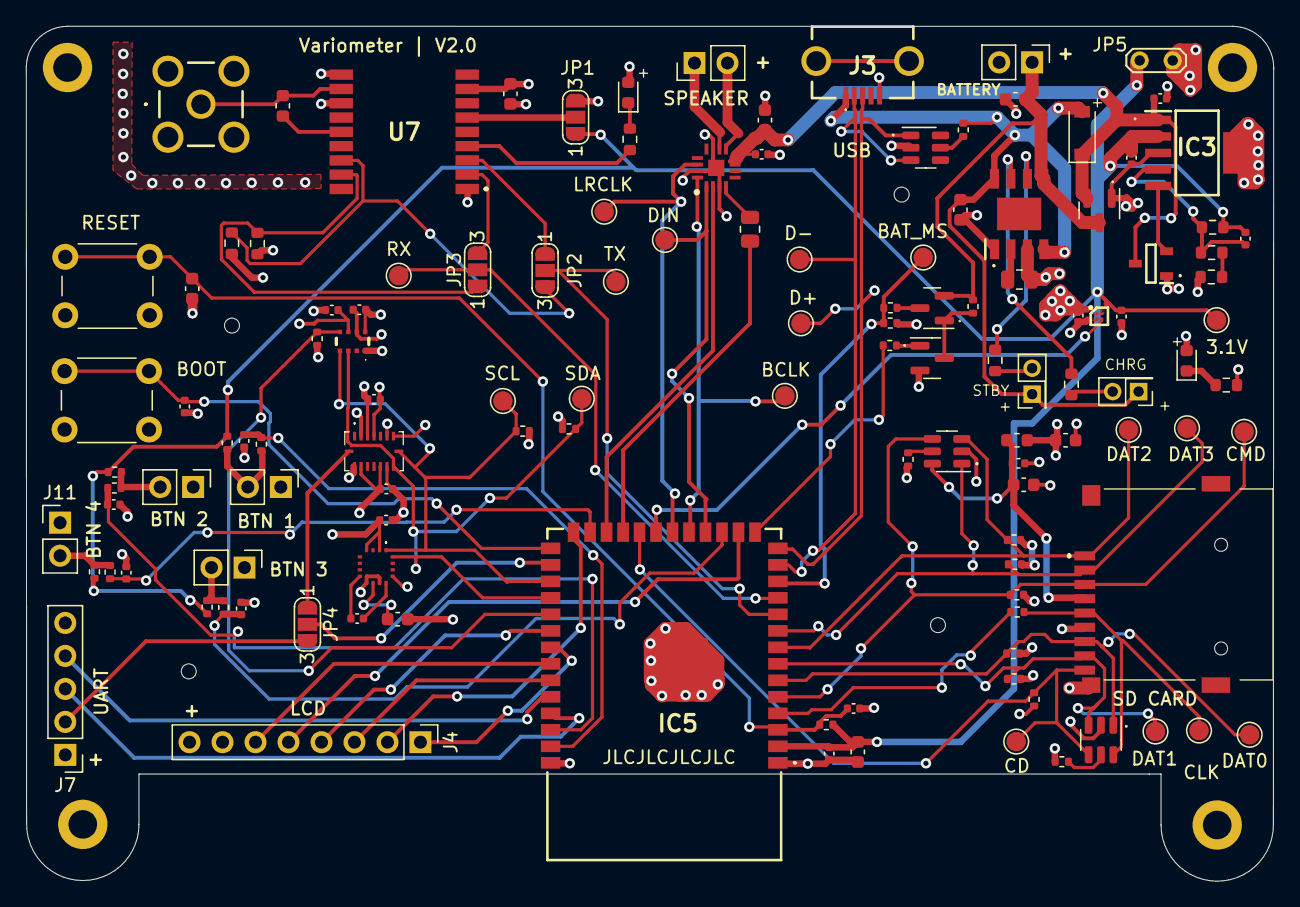
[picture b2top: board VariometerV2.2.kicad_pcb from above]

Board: 4 copper layers, 96.1 x 65.8 mm, 129 parts (0 on the bottom side), 81 nets.

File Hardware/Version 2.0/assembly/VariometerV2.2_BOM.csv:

Comment,Designator,Footprint,LCSC
"10uF","C1,C2,C20,C27","Capacitor_SMD:C_0603_1608Metric","C96446"
"100nF","C11","Capacitor_SMD:C_0603_1608Metric","C14663"
"1uF","C13,C14,C15,C16","Capacitor_SMD:C_0603_1608Metric","C15849"
"2.2uF","C18,C19","Capacitor_SMD:C_0603_1608Metric","C23630"
"220nF","C23","Capacitor_SMD:C_0402_1005Metric","C16772"
"4.7uF","C24","Capacitor_SMD:C_0603_1608Metric","C19666"
"1uF","C3,C5,C6,C10","Capacitor_SMD:C_0402_1005Metric","C52923"
"10nF","C4","Capacitor_SMD:C_0402_1005Metric","C15195"
"100nF","C7,C9,C12,C17,C21,C22,C25,C26,C28,C29","Capacitor_SMD:C_0402_1005Metric","C307331"
"22uF","C8","Capacitor_SMD:C_0603_1608Metric","C59461"
"B5819W SL","D1","Diode_SMD:D_SOD-123","C8598"
"RED","D2","LED_SMD:LED_0603_1608Metric","C2286"
"BLUE","D3","LED_SMD:LED_0603_1608Metric","C72041"
"600 @ 100 MHz","FB1","Inductor_SMD:L_0603_1608Metric","C1002"
"MountingHole_Pad","H1,H2,H3,H4","MountingHole:MountingHole_2.2mm_M2_DIN965_Pad",""
"TP4056","IC1","Hardware:SOIC127P600X175-9N","C16581"
"MAX809STRG","IC2","SamacSys_Parts:SOT96P237X111-3N","C9965"
"TPS73701DCQR","IC3","SamacSys_Parts:SOT127P706X180-6N","C56848"
"TPS22916CNYFPR","IC4","SamacSys_Parts:BGA4C40P2X2_78X78X50","C2655476"
"ESP32-S3-WROOM","IC5","SamacSys_Parts:ESP32S3WROOM1","C2913198"
"LED_CHRG","J1","Connector_PinHeader_2.00mm:PinHeader_2x01_P2.00mm_Vertical",""
"TFP09-2-12B","J12","SamacSys_Parts:TFP09212B",""
"5-1814832-2","J13","Hardware:518148322",""
"LED_STBY","J2","Connector_PinHeader_2.00mm:PinHeader_2x01_P2.00mm_Vertical",""
"USB_B_Micro","J3","Hardware:USB313530A",""
"Conn_01x08","J4","Connector_PinHeader_2.54mm:PinHeader_1x08_P2.54mm_Vertical",""
"Conn_01x02_Male","J5","Connector_PinHeader_2.54mm:PinHeader_1x02_P2.54mm_Vertical",""
"Conn_01x02","J6,J8,J9,J10,J11","Connector_PinHeader_2.54mm:PinHeader_1x02_P2.54mm_Vertical",""
"Conn_01x05","J7","Connector_PinHeader_2.54mm:PinHeader_1x05_P2.54mm_Vertical",""
"SolderJumper_3_Open","JP1,JP2,JP3,JP4","Jumper:SolderJumper-3_P1.3mm_Open_RoundedPad1.0x1.5mm_NumberLabels",""
"47nH","L1","Inductor_SMD:L_0603_1608Metric","C346317"
"AO3401A","Q1,Q2","Package_TO_SOT_SMD:SOT-23","C15127"
"AO3400A","Q3","Package_TO_SOT_SMD:SOT-23","C20917"
"1.2k","R1","Resistor_SMD:R_0805_2012Metric","C17379"
"33k","R10","Resistor_SMD:R_0402_1005Metric","C25779"
"10k","R16,R18,R20,R22,R36,R37","Resistor_SMD:R_0603_1608Metric","C25804"
"1k","R2,R3,R17,R19,R21,R23,R38","Resistor_SMD:R_0603_1608Metric","C21190"
"22","R29","Resistor_SMD:R_0402_1005Metric","C25092"
"0","R33","Resistor_SMD:R_0805_2012Metric","C17477"
"100k","R39","Resistor_SMD:R_0402_1005Metric","C25741"
"47k","R4","Resistor_SMD:R_0603_1608Metric","C25819"
"20k","R5","Resistor_SMD:R_0603_1608Metric","C4184"
"9.1k","R6","Resistor_SMD:R_0603_1608Metric","C23260"
"1.5k","R7","Resistor_SMD:R_0603_1608Metric","C22843"
"1M","R8,R32","Resistor_SMD:R_0402_1005Metric","C26083"
"10k","R9,R11,R12,R15,R24,R25,R26,R27,R28,R30,R31,R34,R35","Resistor_SMD:R_0402_1005Metric","C25744"
"Switch_SW_Push","SW1,SW2","Button_Switch_THT:SW_PUSH_6mm",""
"3.1V TP","TP1","TestPoint:TestPoint_Pad_D1.5mm",""
"TP_CD","TP10","TestPoint:TestPoint_Pad_D1.5mm",""
"TP_BCLK","TP11","TestPoint:TestPoint_Pad_D1.5mm",""
"TP_LRCLK","TP12","TestPoint:TestPoint_Pad_D1.5mm",""
"TP_DIN","TP13","TestPoint:TestPoint_Pad_D1.5mm",""
"TP_SDA","TP14","TestPoint:TestPoint_Pad_D1.5mm",""
"TP_SCL","TP15","TestPoint:TestPoint_Pad_D1.5mm",""
"TP_TX","TP16","TestPoint:TestPoint_Pad_D1.5mm",""
"TP_RX","TP17","TestPoint:TestPoint_Pad_D1.5mm",""
"TP_D+","TP18","TestPoint:TestPoint_Pad_D1.5mm",""
"TP_D-","TP19","TestPoint:TestPoint_Pad_D1.5mm",""
"TP_BATTERY","TP2","TestPoint:TestPoint_Pad_D1.5mm",""
"TP_DAT2","TP3","TestPoint:TestPoint_Pad_D1.5mm",""
"TP_DAT3","TP4","TestPoint:TestPoint_Pad_D1.5mm",""
"TP_CMD","TP5","TestPoint:TestPoint_Pad_D1.5mm",""
"TP_CLK","TP7","TestPoint:TestPoint_Pad_D1.5mm",""
"TP_DAT0","TP8","TestPoint:TestPoint_Pad_D1.5mm",""
"TP_DAT1","TP9","TestPoint:TestPoint_Pad_D1.5mm",""
"SRV05-4","U1,U2,U3","Package_TO_SOT_SMD:SOT-23-6","C85364"
"MAX98357A","U4","SamacSys_Parts:QFN50P300X300X80-17N","C910544"
"QMC5883L","U5","SamacSys_Parts:QMC5883L","C976032"
"BMI088","U6","Hardware:BMI088","C194919"
"ATGM336H-5N31","U7","Hardware:ATGM336H5N31","C90770"
"DPS310","U8","SamacSys_Parts:DPS310XTSA1","C130156"
